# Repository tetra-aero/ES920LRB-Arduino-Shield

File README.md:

# ES920LRB-Arduino-Shield
Arduino Shield for ES920LRB (EASEL), Private LoRa module
- https://easel5.com/service/products-information/products/wireless-module/es920lr2/
- https://easel5.com/documents/files/ES920LR2%E3%83%87%E3%83%BC%E3%82%BF%E3%82%B7%E3%83%BC%E3%83%88_1.04.pdf
- https://easel5.com/documents/files/ES920LRB_BASE%E5%9F%BA%E6%9D%BF%E5%AF%B8%E6%B3%95%E5%9B%B3.pdf

### Ref.
1. https://ambidata.io/samples/network/lora-2/
2. https://qiita.com/nbizyc/items/6f2346ffbe005a5345e9
3. https://github.com/AmbientDataInc/LoRa-rssi-measure

## Schematic, PCB
- Arduino UNO
    - https://github.com/tetra-aero/ES920LRB-Arduino-Shield/tree/main/ES920LRB-Arduino_Uno-Shield
- ESP32 (not shield)
    - https://github.com/tetra-aero/ES920LRB-Arduino-Shield/tree/main/ES920LRB-ESP32

## Firmware
- Arduino UNO, PlatformIO
    - https://github.com/tetra-aero/ES920LRB-Arduino-Shield/tree/main/ES920LRB-Arduino_Uno-Shield/ES920LR-Arduino-PIO
- ESP32, PlatformIO
    - https://github.com/tetra-aero/ES920LRB-Arduino-Shield/tree/main/ES920LRB-ESP32/ESP920LR-Coordinator-ESP32-PIO
    - https://github.com/tetra-aero/ES920LRB-Arduino-Shield/tree/main/ES920LRB-ESP32/ESP920LR-End-device-ESP32-PIO

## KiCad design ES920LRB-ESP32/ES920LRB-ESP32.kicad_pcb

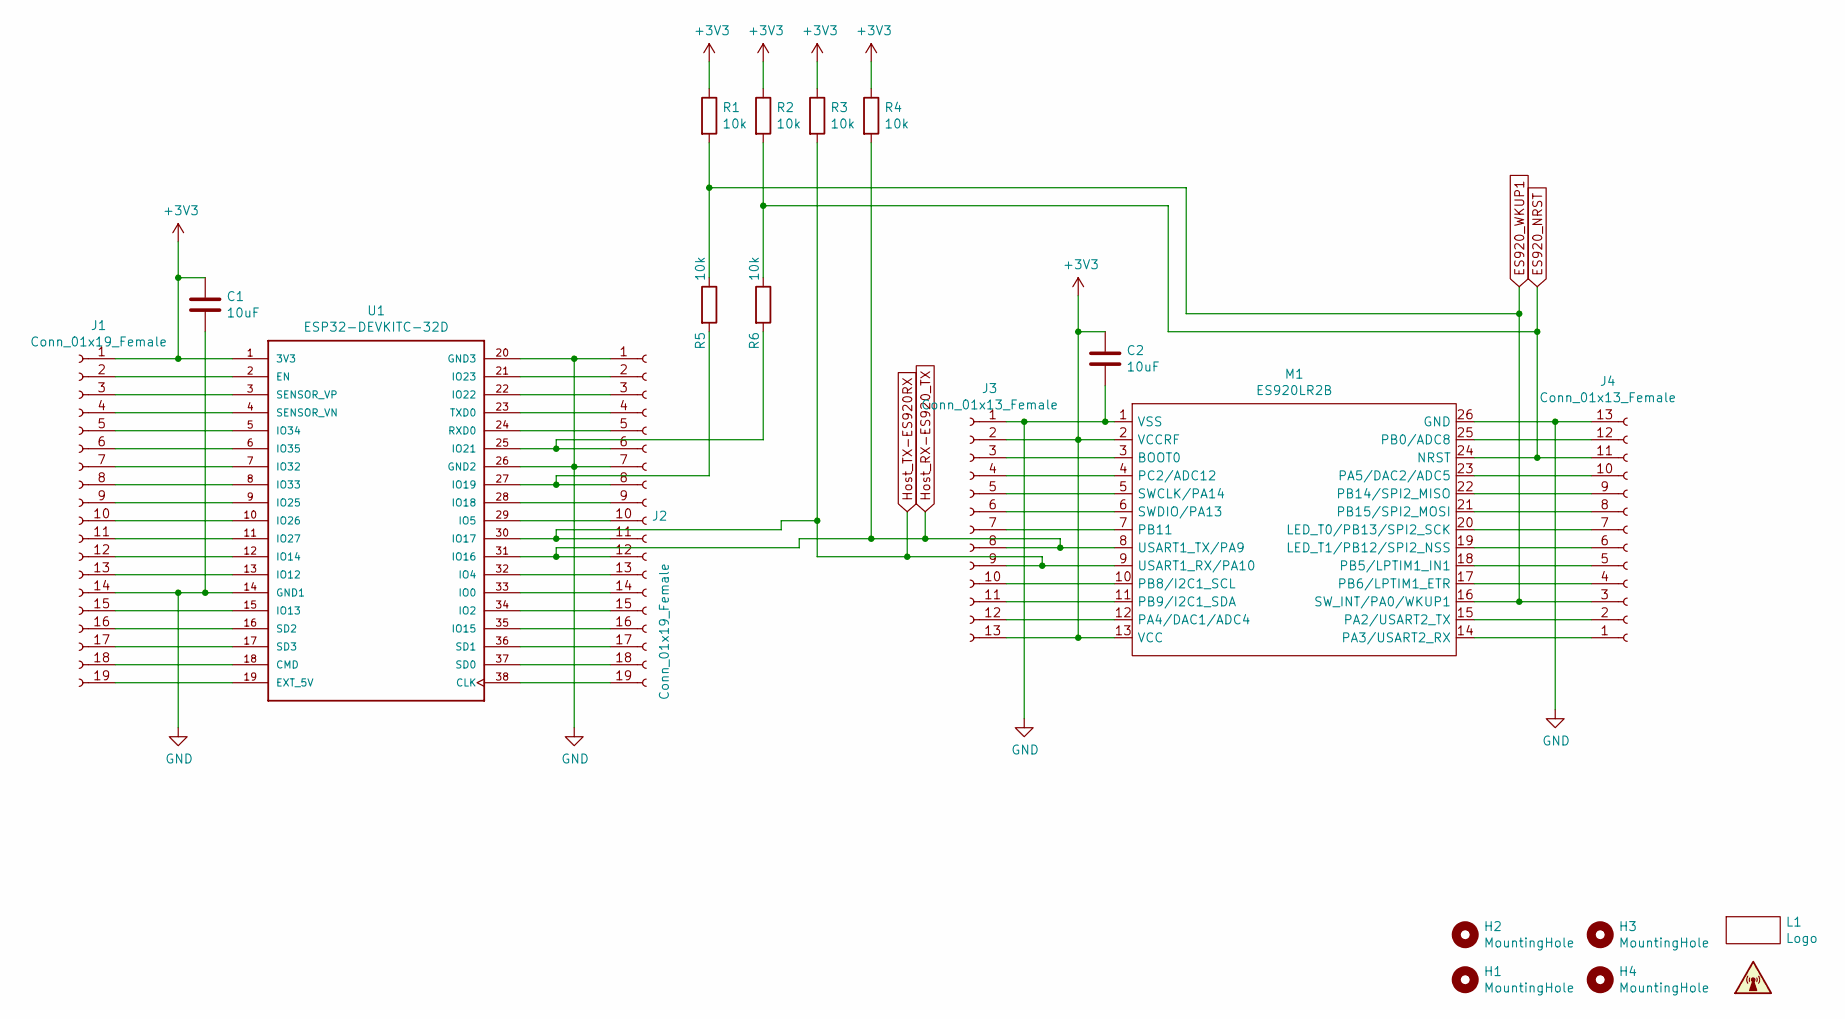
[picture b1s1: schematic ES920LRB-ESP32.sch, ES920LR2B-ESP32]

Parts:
C1, C2: 10uF; C_Rect_L4.0mm_W2.5mm_P2.50mm
H1, H2, H3, H4: MountingHole; MountingHole_3.2mm_M3
J1, J2: Conn_01x19_Female; PinHeader_1x19_P2.54mm_Vertical
J3, J4: Conn_01x13_Female; PinHeader_1x13_P2.54mm_Vertical
L1: Logo; teTra-logo
M1: ES920LR2B; ES92LR2B
R1, R2, R3, R4, R5, R6: 10k; R_Axial_DIN0207_L6.3mm_D2.5mm_P7.62mm_Horizontal
U1: ESP32-DEVKITC-32D; MODULE_ESP32-DEVKITC-32D

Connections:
+3V3: C1.1, C2.1, J1.1, J3.2, J3.13, M1.2 (VCCRF), M1.13 (VCC), R1.1, R2.1, R3.1, R4.1, U1.1 (3V3)
ES920_NRST: J4.11, M1.24 (NRST), R2.2, R6.1
ES920_WKUP1: J4.3, M1.16 (SW_INT/PA0/WKUP1), R1.2, R5.1
GND: C1.2, C2.2, J1.14, J2.1, J2.7, J3.1, J4.13, M1.1 (VSS), M1.26 (GND), U1.14 (GND1), U1.20 (GND3), U1.26 (GND2)
Host_RX-ES920_TX: J2.12, J3.8, M1.8 (USART1_TX/PA9), R4.2, U1.31 (IO16)
Host_TX-ES920RX: J2.11, J3.9, M1.9 (USART1_RX/PA10), R3.2, U1.30 (IO17)
unnamed: J1.2, U1.2 (EN)
unnamed: J1.3, U1.3 (SENSOR_VP)
unnamed: J1.4, U1.4 (SENSOR_VN)
unnamed: J1.5, U1.5 (IO34)
unnamed: J1.6, U1.6 (IO35)
unnamed: J1.7, U1.7 (IO32)
unnamed: J1.8, U1.8 (IO33)
unnamed: J1.9, U1.9 (IO25)
unnamed: J1.10, U1.10 (IO26)
unnamed: J1.11, U1.11 (IO27)
unnamed: J1.12, U1.12 (IO14)
unnamed: J1.13, U1.13 (IO12)
unnamed: J1.15, U1.15 (IO13)
unnamed: J1.16, U1.16 (SD2)
unnamed: J1.17, U1.17 (SD3)
unnamed: J1.18, U1.18 (CMD)
unnamed: J1.19, U1.19 (EXT_5V)
unnamed: J2.2, U1.21 (IO23)
unnamed: J2.3, U1.22 (IO22)
unnamed: J2.4, U1.23 (TXD0)
unnamed: J2.5, U1.24 (RXD0)
unnamed: J2.6, R6.2, U1.25 (IO21)
unnamed: J2.8, R5.2, U1.27 (IO19)
unnamed: J2.9, U1.28 (IO18)
unnamed: J2.10, U1.29 (IO5)
unnamed: J2.13, U1.32 (IO4)
unnamed: J2.14, U1.33 (IO0)
unnamed: J2.15, U1.34 (IO2)
unnamed: J2.16, U1.35 (IO15)
unnamed: J2.17, U1.36 (SD1)
unnamed: J2.18, U1.37 (SD0)
unnamed: J2.19, U1.38 (CLK)
unnamed: J3.3, M1.3 (BOOT0)
unnamed: J3.4, M1.4 (PC2/ADC12)
unnamed: J3.5, M1.5 (SWCLK/PA14)
unnamed: J3.6, M1.6 (SWDIO/PA13)
unnamed: J3.7, M1.7 (PB11)
unnamed: J3.10, M1.10 (PB8/I2C1_SCL)
unnamed: J3.11, M1.11 (PB9/I2C1_SDA)
unnamed: J3.12, M1.12 (PA4/DAC1/ADC4)
unnamed: J4.1, M1.14 (PA3/USART2_RX)
unnamed: J4.2, M1.15 (PA2/USART2_TX)
unnamed: J4.4, M1.17 (PB6/LPTIM1_ETR)
unnamed: J4.5, M1.18 (PB5/LPTIM1_IN1)
unnamed: J4.6, M1.19 (LED_T1/PB12/SPI2_NSS)
unnamed: J4.7, M1.20 (LED_T0/PB13/SPI2_SCK)
unnamed: J4.8, M1.21 (PB15/SPI2_MOSI)
unnamed: J4.9, M1.22 (PB14/SPI2_MISO)
unnamed: J4.10, M1.23 (PA5/DAC2/ADC5)
unnamed: J4.12, M1.25 (PB0/ADC8)

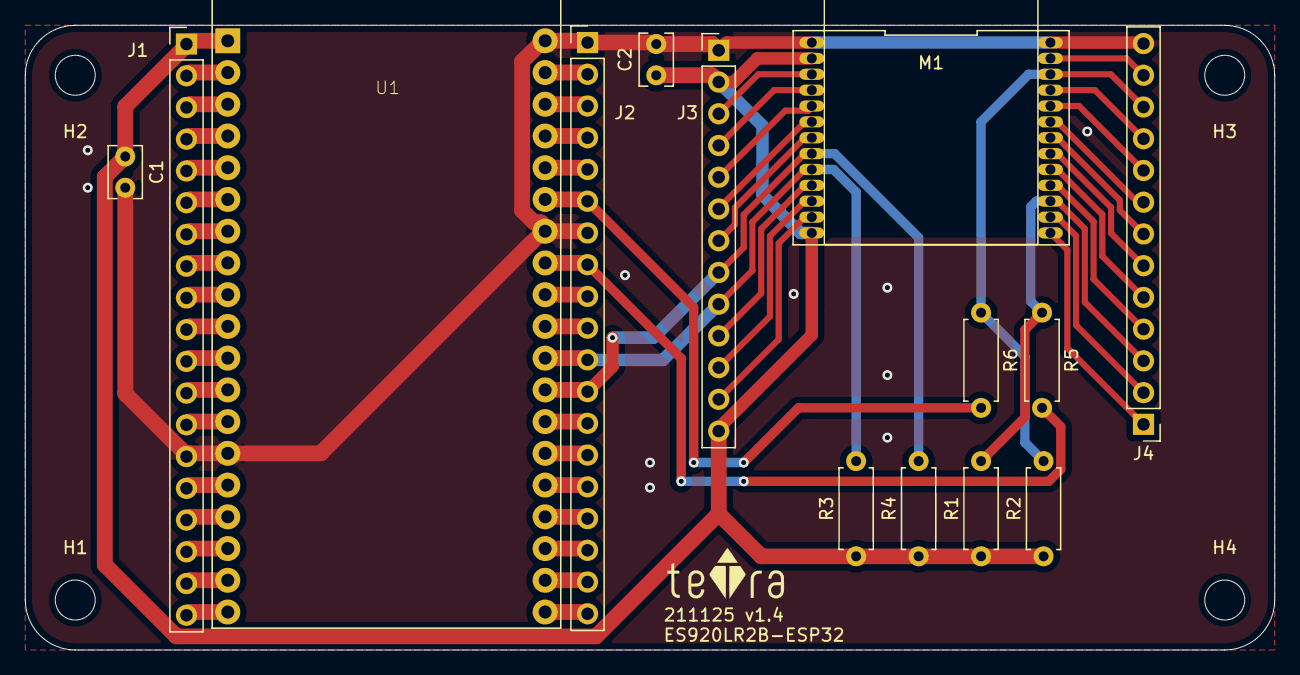
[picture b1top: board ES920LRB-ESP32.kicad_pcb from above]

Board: 2 copper layers, 100.0 x 50.0 mm, 19 parts (0 on the bottom side), 56 nets.

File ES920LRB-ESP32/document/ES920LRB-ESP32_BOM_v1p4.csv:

"Source:","/home/chiya/JetsonWorks/ES920LRB-Arduino-Shield/ES920LRB-ESP32/ES920LRB-ESP32.sch"
"Date:","Wed 24 Nov 2021 08:32:15 PM JST"
"Tool:","Eeschema 5.1.9-73d0e3b20d~88~ubuntu20.04.1"
"Generator:","/usr/share/kicad/plugins/bom_csv_grouped_by_value.py"
"Component Count:","19"

"Individual Components:"

"Item","Qty","Reference(s)","Value","LibPart","Footprint","Datasheet","Field4"
"","","C1","10uF","Device:C","Capacitor_THT:C_Rect_L4.0mm_W2.5mm_P2.50mm","~",""
"","","C2","10uF","Device:C","Capacitor_THT:C_Rect_L4.0mm_W2.5mm_P2.50mm","~",""
"","","H1","MountingHole","Mechanical:MountingHole","MountingHole:MountingHole_3.2mm_M3","~",""
"","","H2","MountingHole","Mechanical:MountingHole","MountingHole:MountingHole_3.2mm_M3","~",""
"","","H3","MountingHole","Mechanical:MountingHole","MountingHole:MountingHole_3.2mm_M3","~",""
"","","H4","MountingHole","Mechanical:MountingHole","MountingHole:MountingHole_3.2mm_M3","~",""
"","","J1","Conn_01x19_Female","Connector:Conn_01x19_Female","Connector_PinHeader_2.54mm:PinHeader_1x19_P2.54mm_Vertical","~",""
"","","J2","Conn_01x19_Female","Connector:Conn_01x19_Female","Connector_PinHeader_2.54mm:PinHeader_1x19_P2.54mm_Vertical","~",""
"","","J3","Conn_01x13_Female","Connector:Conn_01x13_Female","Connector_PinHeader_2.54mm:PinHeader_1x13_P2.54mm_Vertical","~",""
"","","J4","Conn_01x13_Female","Connector:Conn_01x13_Female","Connector_PinHeader_2.54mm:PinHeader_1x13_P2.54mm_Vertical","~",""
"","","L1","Logo","teTra:Logo","teTra:teTra-logo","",""
"","","M1","ES920LR2B","teTra:ES920LR2B","teTra:ES92LR2B","",""
"","","R1","10k","Device:R","Resistor_THT:R_Axial_DIN0207_L6.3mm_D2.5mm_P7.62mm_Horizontal","~",""
"","","R2","10k","Device:R","Resistor_THT:R_Axial_DIN0207_L6.3mm_D2.5mm_P7.62mm_Horizontal","~",""
"","","R3","10k","Device:R","Resistor_THT:R_Axial_DIN0207_L6.3mm_D2.5mm_P7.62mm_Horizontal","~",""
"","","R4","10k","Device:R","Resistor_THT:R_Axial_DIN0207_L6.3mm_D2.5mm_P7.62mm_Horizontal","~",""
"","","R5","10k","Device:R","Resistor_THT:R_Axial_DIN0207_L6.3mm_D2.5mm_P7.62mm_Horizontal","~",""
"","","R6","10k","Device:R","Resistor_THT:R_Axial_DIN0207_L6.3mm_D2.5mm_P7.62mm_Horizontal","~",""
"","","U1","ESP32-DEVKITC-32D","ESP32_32D_module:ESP32-DEVKITC-32D","MODULE_ESP32-DEVKITC-32D","Espressif Systems","4"



"Collated Components:"

"Item","Qty","Reference(s)","Value","LibPart","Footprint","Datasheet","Field4"
"1","2","C1, C2","10uF","Device:C","Capacitor_THT:C_Rect_L4.0mm_W2.5mm_P2.50mm","~",""
"2","4","H1, H2, H3, H4","MountingHole","Mechanical:MountingHole","MountingHole:MountingHole_3.2mm_M3","~",""
"3","2","J1, J2","Conn_01x19_Female","Connector:Conn_01x19_Female","Connector_PinHeader_2.54mm:PinHeader_1x19_P2.54mm_Vertical","~",""
"4","2","J3, J4","Conn_01x13_Female","Connector:Conn_01x13_Female","Connector_PinHeader_2.54mm:PinHeader_1x13_P2.54mm_Vertical","~",""
"5","1","L1","Logo","teTra:Logo","teTra:teTra-logo","",""
"6","1","M1","ES920LR2B","teTra:ES920LR2B","teTra:ES92LR2B","",""
"7","6","R1, R2, R3, R4, R5, R6","10k","Device:R","Resistor_THT:R_Axial_DIN0207_L6.3mm_D2.5mm_P7.62mm_Horizontal","~",""
"8","1","U1","ESP32-DEVKITC-32D","ESP32_32D_module:ESP32-DEVKITC-32D","MODULE_ESP32-DEVKITC-32D","Espressif Systems","4"

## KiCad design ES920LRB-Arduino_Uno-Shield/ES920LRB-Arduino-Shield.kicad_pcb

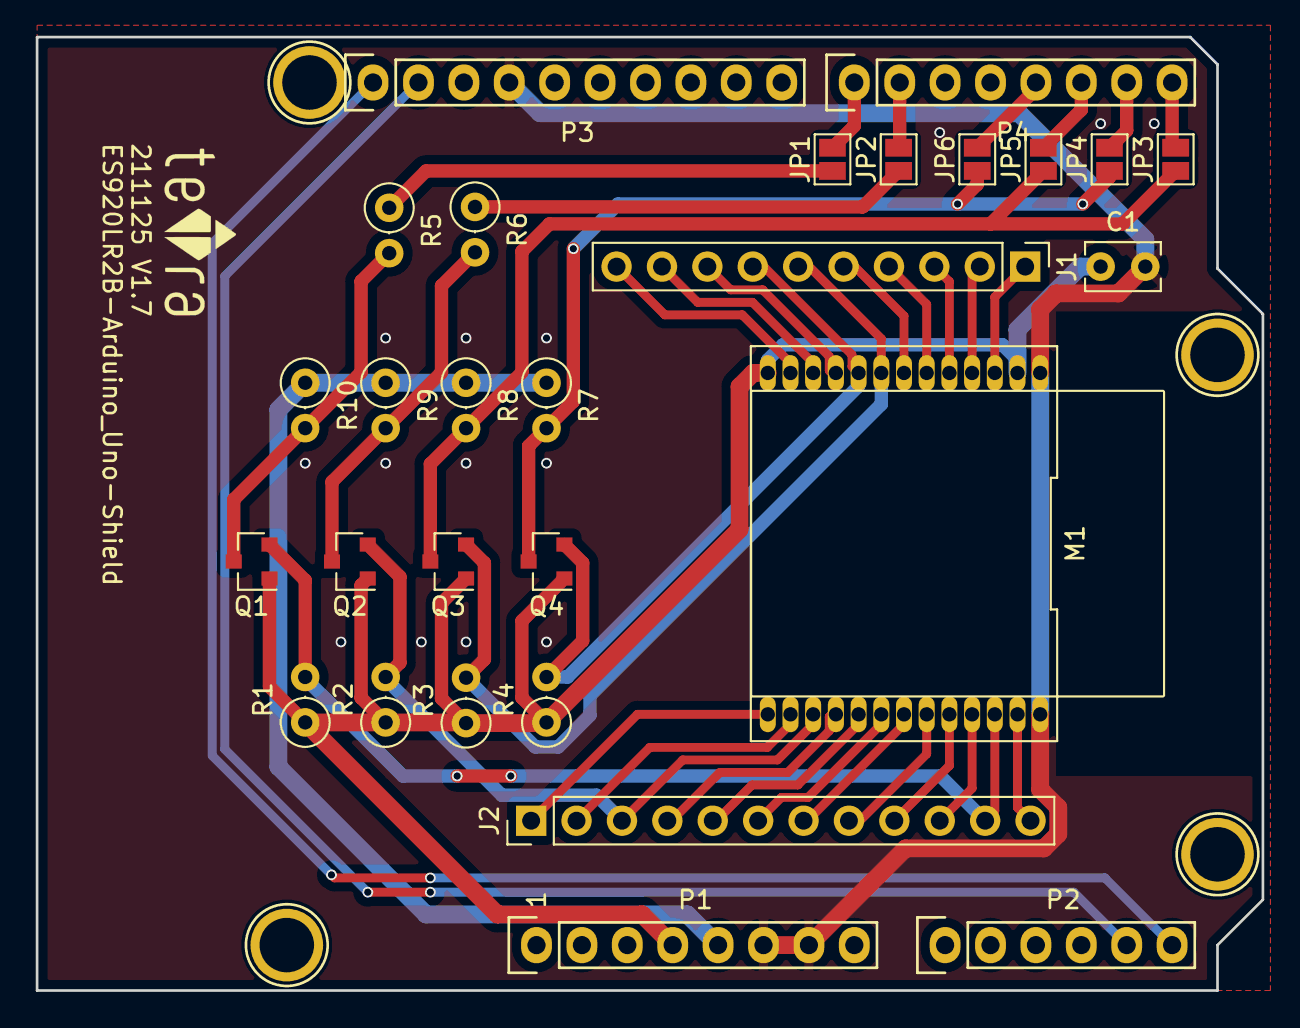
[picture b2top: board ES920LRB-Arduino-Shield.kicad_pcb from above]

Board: 2 copper layers, 68.6 x 53.3 mm, 33 parts (0 on the bottom side), 39 nets.

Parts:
C1: 10uF; C_Rect_L4.0mm_W2.5mm_P2.50mm
J1: Conn_01x10_Female; PinHeader_1x10_P2.54mm_Vertical
J2: Conn_01x12_Female; PinHeader_1x12_P2.54mm_Vertical
JP1, JP2, JP3, JP4, JP5, JP6: SolderJumper_2_Open; SolderJumper-2_P1.3mm_Open_Pad1.0x1.5mm
L1: Logo; teTra-logo
M1: ES920LR2B; ES92LR2B
P1: Power; Socket_Strip_Arduino_1x08
P2: Analog; Socket_Strip_Arduino_1x06
P3: Digital; Socket_Strip_Arduino_1x10
P4: Digital; Socket_Strip_Arduino_1x08
P5, P6, P7, P8: CONN_01X01; Arduino_1pin
Q1, Q2, Q3, Q4: BSS138; SOT-23
R1, R2, R3, R4, R5, R6, R7, R8, R9, R10: 10k; R_Axial_DIN0207_L6.3mm_D2.5mm_P2.54mm_Vertical

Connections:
+3V3: C1.1, M1.2, M1.13, P1.4, Q1.1, Q2.1, Q3.1, Q4.1, R1.1, R2.1, R3.1, R4.1
+5V: P1.5, R7.1, R8.1, R9.1, R10.1
/0(Rx): JP3.2, P4.8
/1(Tx): JP4.2, P4.7
/2: JP5.2, P4.6
/3(**): JP6.2, P4.5
/6(**): JP2.2, P4.2
/7: JP1.2, P4.1
/A4(SDA): P2.5, P3.2
/A5(SCL): P2.6, P3.1
GND: C1.2, M1.1, M1.26, P1.6, P1.7, P3.4
unnamed: J1.1, M1.3
unnamed: J1.2, M1.4
unnamed: J1.3, M1.5
unnamed: J1.4, M1.6
unnamed: J1.5, M1.7
unnamed: J1.6, M1.8, Q3.2, R3.2
unnamed: J1.7, M1.9, Q4.2, R4.2
unnamed: J1.8, M1.10
unnamed: J1.9, M1.11
unnamed: J1.10, M1.12
unnamed: J2.1, M1.14
unnamed: J2.2, M1.15
unnamed: J2.3, M1.16, Q2.2, R2.2
unnamed: J2.4, M1.17
unnamed: J2.5, M1.18
unnamed: J2.6, M1.19
unnamed: J2.7, M1.20
unnamed: J2.8, M1.21
unnamed: J2.9, M1.22
unnamed: J2.10, M1.23
unnamed: J2.11, M1.24, Q1.2, R1.2
unnamed: J2.12, M1.25
unnamed: JP1.1, R5.1
unnamed: JP2.1, R6.1
unnamed: JP3.1, JP5.1, Q3.3, R8.2
unnamed: JP4.1, JP6.1, Q4.3, R7.2
unnamed: Q1.3, R5.2, R10.2
unnamed: Q2.3, R6.2, R9.2

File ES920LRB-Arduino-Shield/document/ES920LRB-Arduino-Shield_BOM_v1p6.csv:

"Source:","/home/chiya/JetsonWorks/ES920LRB-Arduino-Shield/ES920LRB-Arduino-Shield/ES920LRB-Arduino-Shield.sch"
"Date:","Wed 24 Nov 2021 06:48:10 PM JST"
"Tool:","Eeschema 5.1.9-73d0e3b20d~88~ubuntu20.04.1"
"Generator:","/usr/share/kicad/plugins/bom_csv_grouped_by_value.py"
"Component Count:","33"

"Individual Components:"

"Item","Qty","Reference(s)","Value","LibPart","Footprint","Datasheet"
"","","C1","10uF","Device:C","Capacitor_THT:C_Rect_L4.0mm_W2.5mm_P2.50mm","~"
"","","J1","Conn_01x10_Female","Connector:Conn_01x10_Female","Connector_PinHeader_2.54mm:PinHeader_1x10_P2.54mm_Vertical","~"
"","","J2","Conn_01x12_Female","Connector:Conn_01x12_Female","Connector_PinHeader_2.54mm:PinHeader_1x12_P2.54mm_Vertical","~"
"","","JP1","SolderJumper_2_Open","Jumper:SolderJumper_2_Open","Jumper:SolderJumper-2_P1.3mm_Open_Pad1.0x1.5mm","~"
"","","JP2","SolderJumper_2_Open","Jumper:SolderJumper_2_Open","Jumper:SolderJumper-2_P1.3mm_Open_Pad1.0x1.5mm","~"
"","","JP3","SolderJumper_2_Open","Jumper:SolderJumper_2_Open","Jumper:SolderJumper-2_P1.3mm_Open_Pad1.0x1.5mm","~"
"","","JP4","SolderJumper_2_Open","Jumper:SolderJumper_2_Open","Jumper:SolderJumper-2_P1.3mm_Open_Pad1.0x1.5mm","~"
"","","JP5","SolderJumper_2_Open","Jumper:SolderJumper_2_Open","Jumper:SolderJumper-2_P1.3mm_Open_Pad1.0x1.5mm","~"
"","","JP6","SolderJumper_2_Open","Jumper:SolderJumper_2_Open","Jumper:SolderJumper-2_P1.3mm_Open_Pad1.0x1.5mm","~"
"","","L1","Logo","teTra:Logo","teTra:teTra-logo",""
"","","M1","ES920LR2B","teTra:ES920LR2B","teTra:ES92LR2B",""
"","","P1","Power","Connector_Generic:Conn_01x08","Socket_Arduino_Uno:Socket_Strip_Arduino_1x08",""
"","","P2","Analog","Connector_Generic:Conn_01x06","Socket_Arduino_Uno:Socket_Strip_Arduino_1x06",""
"","","P3","Digital","Connector_Generic:Conn_01x10","Socket_Arduino_Uno:Socket_Strip_Arduino_1x10",""
"","","P4","Digital","Connector_Generic:Conn_01x08","Socket_Arduino_Uno:Socket_Strip_Arduino_1x08",""
"","","P5","CONN_01X01","Connector_Generic:Conn_01x01","Socket_Arduino_Uno:Arduino_1pin",""
"","","P6","CONN_01X01","Connector_Generic:Conn_01x01","Socket_Arduino_Uno:Arduino_1pin",""
"","","P7","CONN_01X01","Connector_Generic:Conn_01x01","Socket_Arduino_Uno:Arduino_1pin",""
"","","P8","CONN_01X01","Connector_Generic:Conn_01x01","Socket_Arduino_Uno:Arduino_1pin",""
"","","Q1","BSS138","add_lib2:BSS138","Package_TO_SOT_SMD:SOT-23","https://www.onsemi.com/pub/Collateral/BSS138-D.PDF"
"","","Q2","BSS138","add_lib2:BSS138","Package_TO_SOT_SMD:SOT-23","https://www.onsemi.com/pub/Collateral/BSS138-D.PDF"
"","","Q3","BSS138","add_lib2:BSS138","Package_TO_SOT_SMD:SOT-23","https://www.onsemi.com/pub/Collateral/BSS138-D.PDF"
"","","Q4","BSS138","add_lib2:BSS138","Package_TO_SOT_SMD:SOT-23","https://www.onsemi.com/pub/Collateral/BSS138-D.PDF"
"","","R1","10k","Device:R","Resistor_THT:R_Axial_DIN0207_L6.3mm_D2.5mm_P2.54mm_Vertical","~"
"","","R2","10k","Device:R","Resistor_THT:R_Axial_DIN0207_L6.3mm_D2.5mm_P2.54mm_Vertical","~"
"","","R3","10k","Device:R","Resistor_THT:R_Axial_DIN0207_L6.3mm_D2.5mm_P2.54mm_Vertical","~"
"","","R4","10k","Device:R","Resistor_THT:R_Axial_DIN0207_L6.3mm_D2.5mm_P2.54mm_Vertical","~"
"","","R5","10k","Device:R","Resistor_THT:R_Axial_DIN0207_L6.3mm_D2.5mm_P2.54mm_Vertical","~"
"","","R6","10k","Device:R","Resistor_THT:R_Axial_DIN0207_L6.3mm_D2.5mm_P2.54mm_Vertical","~"
"","","R7","10k","Device:R","Resistor_THT:R_Axial_DIN0207_L6.3mm_D2.5mm_P2.54mm_Vertical","~"
"","","R8","10k","Device:R","Resistor_THT:R_Axial_DIN0207_L6.3mm_D2.5mm_P2.54mm_Vertical","~"
"","","R9","10k","Device:R","Resistor_THT:R_Axial_DIN0207_L6.3mm_D2.5mm_P2.54mm_Vertical","~"
"","","R10","10k","Device:R","Resistor_THT:R_Axial_DIN0207_L6.3mm_D2.5mm_P2.54mm_Vertical","~"



"Collated Components:"

"Item","Qty","Reference(s)","Value","LibPart","Footprint","Datasheet"
"1","1","C1","10uF","Device:C","Capacitor_THT:C_Rect_L4.0mm_W2.5mm_P2.50mm","~"
"2","1","J1","Conn_01x10_Female","Connector:Conn_01x10_Female","Connector_PinHeader_2.54mm:PinHeader_1x10_P2.54mm_Vertical","~"
"3","1","J2","Conn_01x12_Female","Connector:Conn_01x12_Female","Connector_PinHeader_2.54mm:PinHeader_1x12_P2.54mm_Vertical","~"
"4","6","JP1, JP2, JP3, JP4, JP5, JP6","SolderJumper_2_Open","Jumper:SolderJumper_2_Open","Jumper:SolderJumper-2_P1.3mm_Open_Pad1.0x1.5mm","~"
"5","1","L1","Logo","teTra:Logo","teTra:teTra-logo",""
"6","1","M1","ES920LR2B","teTra:ES920LR2B","teTra:ES92LR2B",""
"7","1","P1","Power","Connector_Generic:Conn_01x08","Socket_Arduino_Uno:Socket_Strip_Arduino_1x08",""
"8","1","P2","Analog","Connector_Generic:Conn_01x06","Socket_Arduino_Uno:Socket_Strip_Arduino_1x06",""
"9","1","P3","Digital","Connector_Generic:Conn_01x10","Socket_Arduino_Uno:Socket_Strip_Arduino_1x10",""
"10","1","P4","Digital","Connector_Generic:Conn_01x08","Socket_Arduino_Uno:Socket_Strip_Arduino_1x08",""
"11","4","P5, P6, P7, P8","CONN_01X01","Connector_Generic:Conn_01x01","Socket_Arduino_Uno:Arduino_1pin",""
"12","4","Q1, Q2, Q3, Q4","BSS138","add_lib2:BSS138","Package_TO_SOT_SMD:SOT-23","https://www.onsemi.com/pub/Collateral/BSS138-D.PDF"
"13","10","R1, R2, R3, R4, R5, R6, R7, R8, R9, R10","10k","Device:R","Resistor_THT:R_Axial_DIN0207_L6.3mm_D2.5mm_P2.54mm_Vertical","~"

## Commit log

2021-11-16 add v1.1
    add v1.1
2021-11-18 add v1.2
    add v1.2
2021-11-18 5V <---> 3V3変換が必要じゃん、add esp32 under construction
    5V <---> 3V3変換が必要じゃん、add esp32 under construction
2021-11-19 esp32 coordinator and end device under construction
    esp32 coordinator and end device under construction
2021-11-19 success esp32 communication
    success esp32 communication
2021-11-19 success esp32 count
    success esp32 count
2021-11-24 add schematica v1.3
    add schematica v1.3
2021-11-24 add v1.4
    add v1.4
2021-11-24 add arduino uno sheild pcb
    add arduino uno sheild pcb
2021-11-24 add arduino uno shield v1.6
    add arduino uno shield v1.6
2021-11-24 add ES920LRB-ESP32 v1.4
    add ES920LRB-ESP32 v1.4
2021-11-24 add ES920LRB-ESP32 v1.4 BOM
    add ES920LRB-ESP32 v1.4 BOM
2021-11-25 order pcb v1.x
    order pcb v1.x
2021-11-26 add readme
    add readme
